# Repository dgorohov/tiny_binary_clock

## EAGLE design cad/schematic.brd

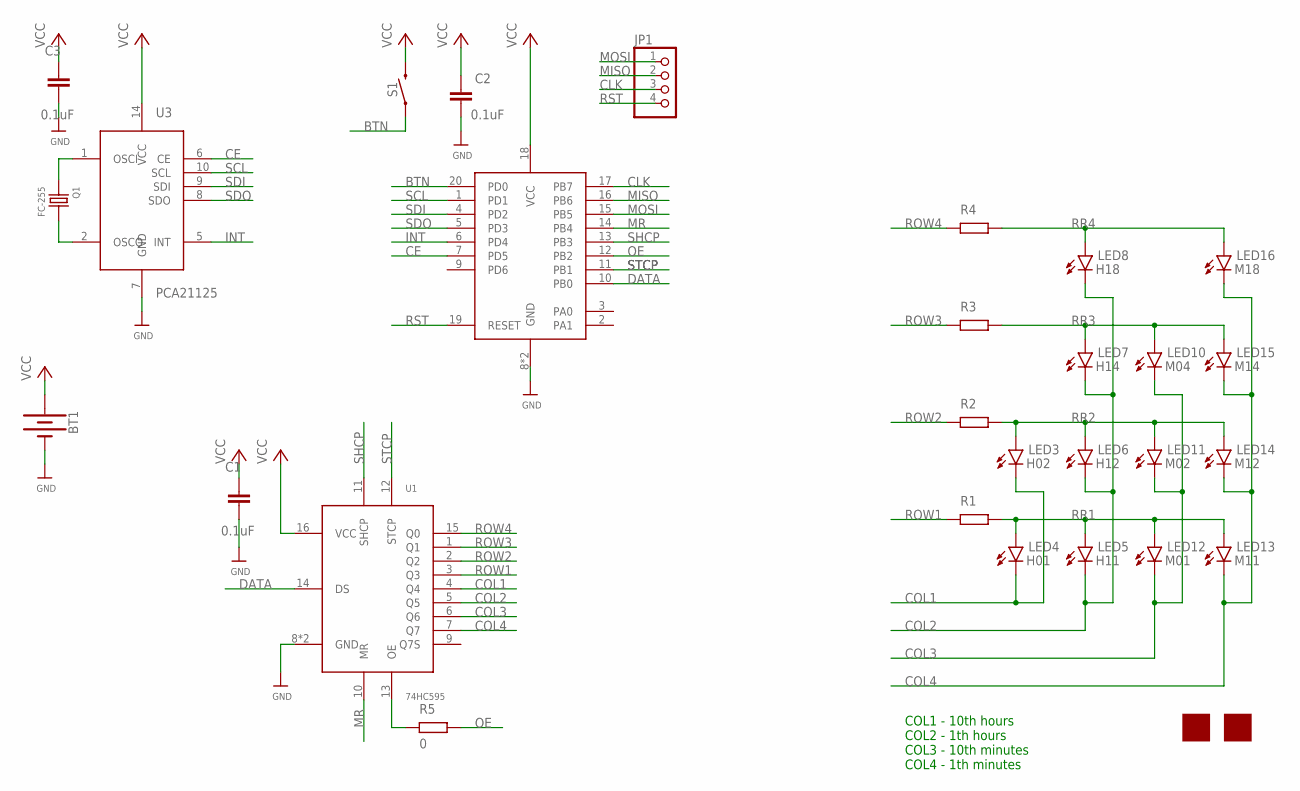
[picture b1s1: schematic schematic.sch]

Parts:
BT1: BATTERY-12MM_SMD; BATTCON_12MM
C1, C2, C3: 0.1uF; CAP_0402
IMG1: IMAGE; IMG6
IMG2: SLOT
JP1: PINHD-1X4; 1X04
LED3: H02; LG-T67K
LED4: H01; LG-T67K
LED5: H11; LG-T67K
LED6: H12; LG-T67K
LED7: H14; LG-T67K
LED8: H18; LG-T67K
LED10: M04; LG-T67K
LED11: M02; LG-T67K
LED12: M01; LG-T67K
LED13: M11; LG-T67K
LED14: M12; LG-T67K
LED15: M14; LG-T67K
LED16: M18; LG-T67K
Q1: FC-255
R1, R2, R3, R4: R_CHIP-0402(1005-METRIC); RESC1005X40
R5: 0; RESC1005X40
S1: MOMENTARY-SWITCH-SPST-SMD-6.2MM-TALL; TACTILE_SWITCH_SMD_6.2MM_TALL
U1: 74HC595; DHVQFN16
U2: ATTINY2313; QFN20-.45MMPITCH
U3: PCA21125; TSSOP14

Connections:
BTN: S1.A2 (1), U2.20 (PD0)
CE: U2.7 (PD5), U3.6 (CE)
CLK: JP1.3, U2.17 (PB7)
COL1: LED3.P$2 (C), LED4.P$2 (C), U1.4 (Q4)
COL2: LED5.P$2 (C), LED6.P$2 (C), LED7.P$2 (C), LED8.P$2 (C), U1.5 (Q5)
COL3: LED10.P$2 (C), LED11.P$2 (C), LED12.P$2 (C), U1.6 (Q6)
COL4: LED13.P$2 (C), LED14.P$2 (C), LED15.P$2 (C), LED16.P$2 (C), U1.7 (Q7)
DATA: U1.14 (DS), U2.10 (PB0)
GND: BT1.GND (-), C1.2, C2.2, C3.2, U1.8 (GND), U1.PAD (GND), U2.8 (GND), U2.21 (GND), U3.7 (GND)
INT: U2.6 (PD4), U3.5 (INT)
MISO: JP1.2, U2.16 (PB6)
MOSI: JP1.1, U2.15 (PB5)
MR: U1.10 (MR), U2.14 (PB4)
unnamed: Q1.OUT (2), U3.2 (OSCO)
unnamed: Q1.IN (1), U3.1 (OSCI)
unnamed: R5.1, U1.13 (OE)
OE: R5.2, U2.12 (PB2)
ROW1: R1.1, U1.3 (Q3)
ROW2: R2.1, U1.2 (Q2)
ROW3: R3.1, U1.1 (Q1)
ROW4: R4.1, U1.15 (Q0)
RR1: LED4.P$1 (A), LED5.P$1 (A), LED12.P$1 (A), LED13.P$1 (A), R1.2
RR2: LED3.P$1 (A), LED6.P$1 (A), LED11.P$1 (A), LED14.P$1 (A), R2.2
RR3: LED7.P$1 (A), LED10.P$1 (A), LED15.P$1 (A), R3.2
RR4: LED8.P$1 (A), LED16.P$1 (A), R4.2
RST: JP1.4, U2.19 (RESET)
SCL: U2.1 (PD1), U3.10 (SCL)
SDI: U2.4 (PD2), U3.9 (SDI)
SDO: U2.5 (PD3), U3.8 (SDO)
SHCP: U1.11 (SHCP), U2.13 (PB3)
STCP: U1.12 (STCP), U2.11 (PB1)
VCC: BT1.PWR@1 (+), C1.1, C2.1, C3.1, S1.B2 (2), U1.16 (VCC), U2.18 (VCC), U3.14 (VCC)

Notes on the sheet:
COL1 - 10th hours COL2 - 1th hours COL3 - 10th minutes COL4 - 1th minutes

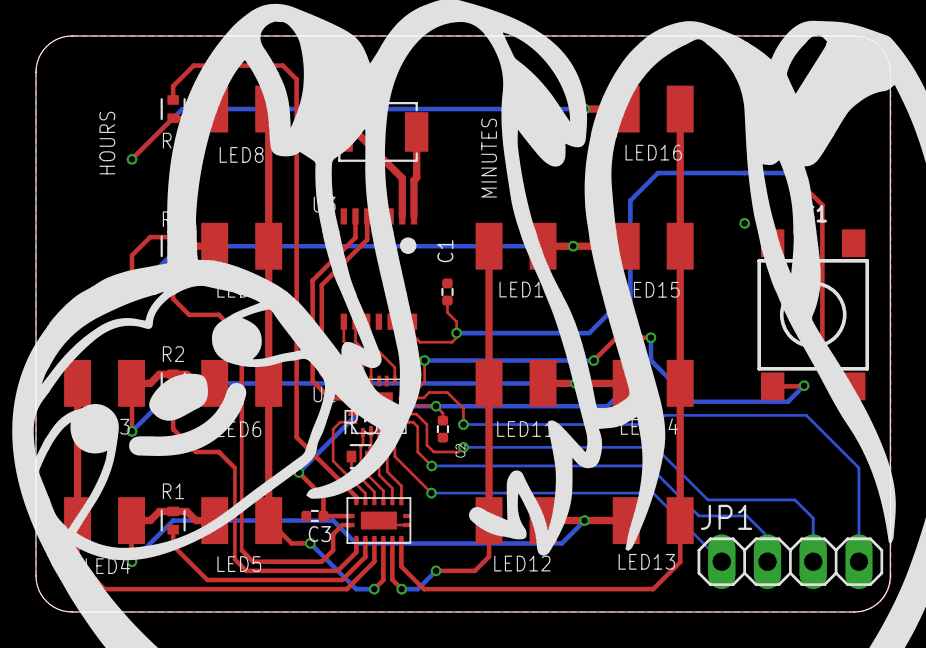
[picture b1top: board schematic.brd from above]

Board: 2 copper layers, 47.5 x 32.0 mm, 30 parts (1 on the bottom side), 32 nets.

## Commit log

2020-05-28 RTC fixes
2020-11-13 pdf attached

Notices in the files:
parts and their libraries:
SparkFun-Batteries: Licensing: Creative Commons ShareAlike 4.0 International - https://creativecommons.org/licenses/by-sa/4.0
